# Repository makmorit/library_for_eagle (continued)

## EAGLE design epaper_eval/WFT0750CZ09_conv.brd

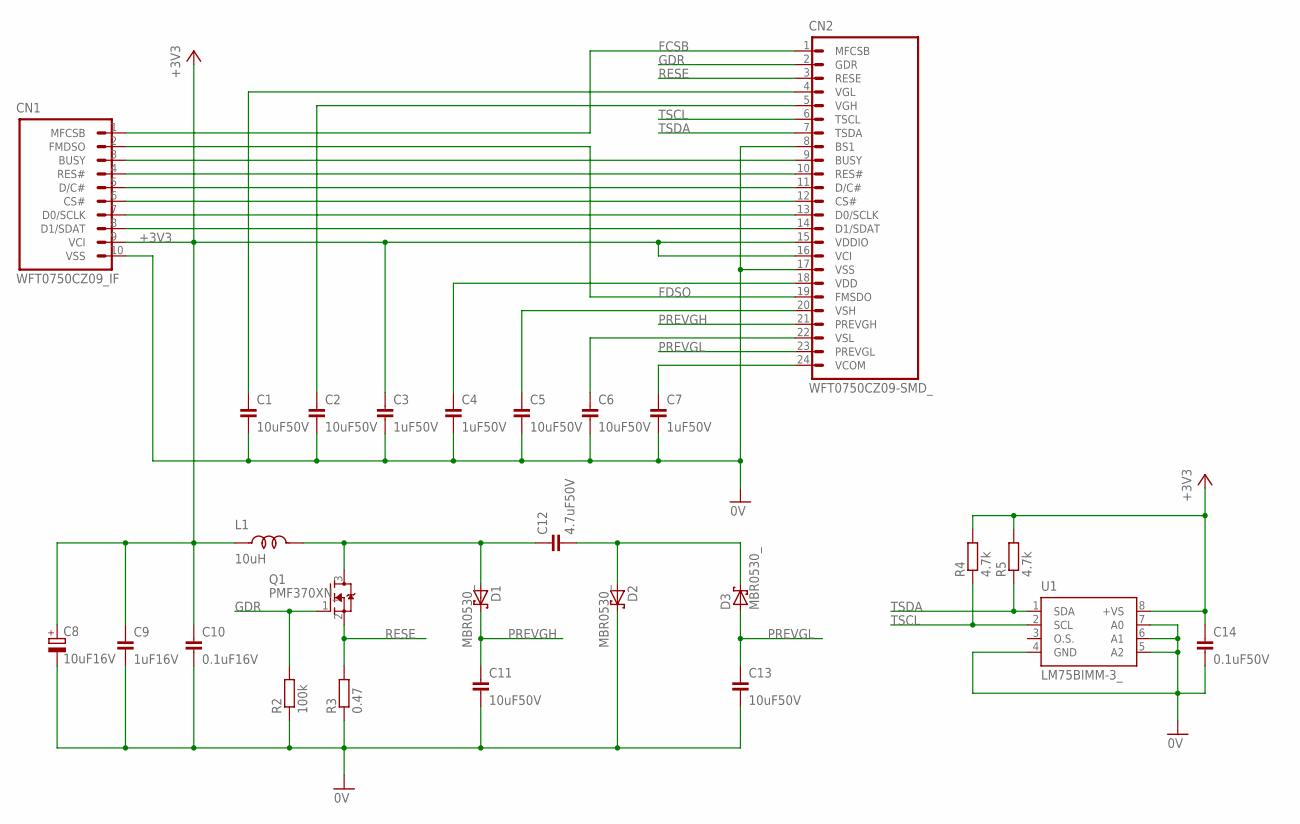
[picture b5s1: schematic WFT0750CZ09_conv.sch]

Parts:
C1, C2, C5, C6, C11, C13: 10uF50V; SMD_2012
C3, C4, C7: 1uF50V; SMD_2012
C8: 10uF16V; C1210_TPST_DEV
C9: 1uF16V; SMD_2012
C10: 0.1uF16V; SMD_2012
C12: 4.7uF50V; SMD_2012
C14: 0.1uF50V; SMD_2012
CN1: WFT0750CZ09_IF; WFT0750CZ09_IF_10PIN
CN2: WFT0750CZ09-SMD_; FH12A-24S-0.5SH_DEV
D1, D2, D3: MBR0530_; MBR0530_DEV
L1: 10uH; NLCV25T_DEV
Q1: PMF370XN_; SOT323_DEV
R2: 100k; SMD_2012
R3: 0.47; SMD_2012
R4, R5: 4.7k; SMD_2012
U1: LM75BIMM-3_; SSOP8-DGK_DEV

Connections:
0V: C1.2, C2.2, C3.2, C4.2, C5.2, C6.2, C7.2, C8.2 (-), C9.2, C10.2, C11.2, C13.2, C14.2, CN1.10 (VSS), CN2.8 (BS1), CN2.17 (VSS), D2.1 (C), R2.1, R3.1, U1.4 (GND), U1.5 (A2), U1.6 (A1), U1.7 (A0)
+3V3: C3.1, C8.1 (+), C9.1, C10.1, C14.1, CN1.9 (VCI), CN2.15 (VDDIO), CN2.16 (VCI), L1.1, R4.2, R5.2, U1.8 (+VS)
FCSB: CN1.1 (MFCSB), CN2.1 (MFCSB)
FDSO: CN1.2 (FMDSO), CN2.19 (FMSDO)
GDR: CN2.2 (GDR), Q1.1 (G), R2.2
unnamed: C7.1, CN2.24 (VCOM)
unnamed: C6.1, CN2.22 (VSL)
unnamed: C5.1, CN2.20 (VSH)
unnamed: C4.1, CN2.18 (VDD)
unnamed: C12.1, D1.2 (A), L1.2, Q1.3 (D)
unnamed: C2.1, CN2.5 (VGH)
unnamed: C1.1, CN2.4 (VGL)
unnamed: CN1.3 (BUSY), CN2.9 (BUSY)
unnamed: CN1.4 (RES#), CN2.10 (RES#)
unnamed: CN1.5 (D/C#), CN2.11 (D/C#)
unnamed: CN1.6 (CS#), CN2.12 (CS#)
unnamed: CN1.7 (D0/SCLK), CN2.13 (D0/SCLK)
unnamed: CN1.8 (D1/SDAT), CN2.14 (D1/SDAT)
unnamed: C12.2, D2.2 (A), D3.1 (C)
PREVGH: C11.1, CN2.21 (PREVGH), D1.1 (C)
PREVGL: C13.1, CN2.23 (PREVGL), D3.2 (A)
RESE: CN2.3 (RESE), Q1.2 (S), R3.2
TSCL: CN2.6 (TSCL), R4.1, U1.2 (SCL)
TSDA: CN2.7 (TSDA), R5.1, U1.1 (SDA)

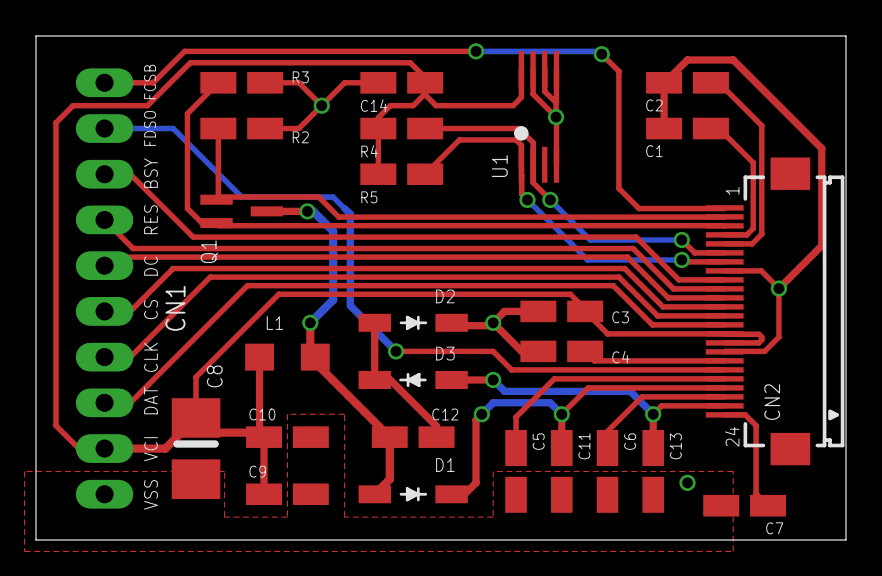
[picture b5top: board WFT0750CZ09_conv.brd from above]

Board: 2 copper layers, 45.0 x 28.0 mm, 26 parts (0 on the bottom side), 24 nets.

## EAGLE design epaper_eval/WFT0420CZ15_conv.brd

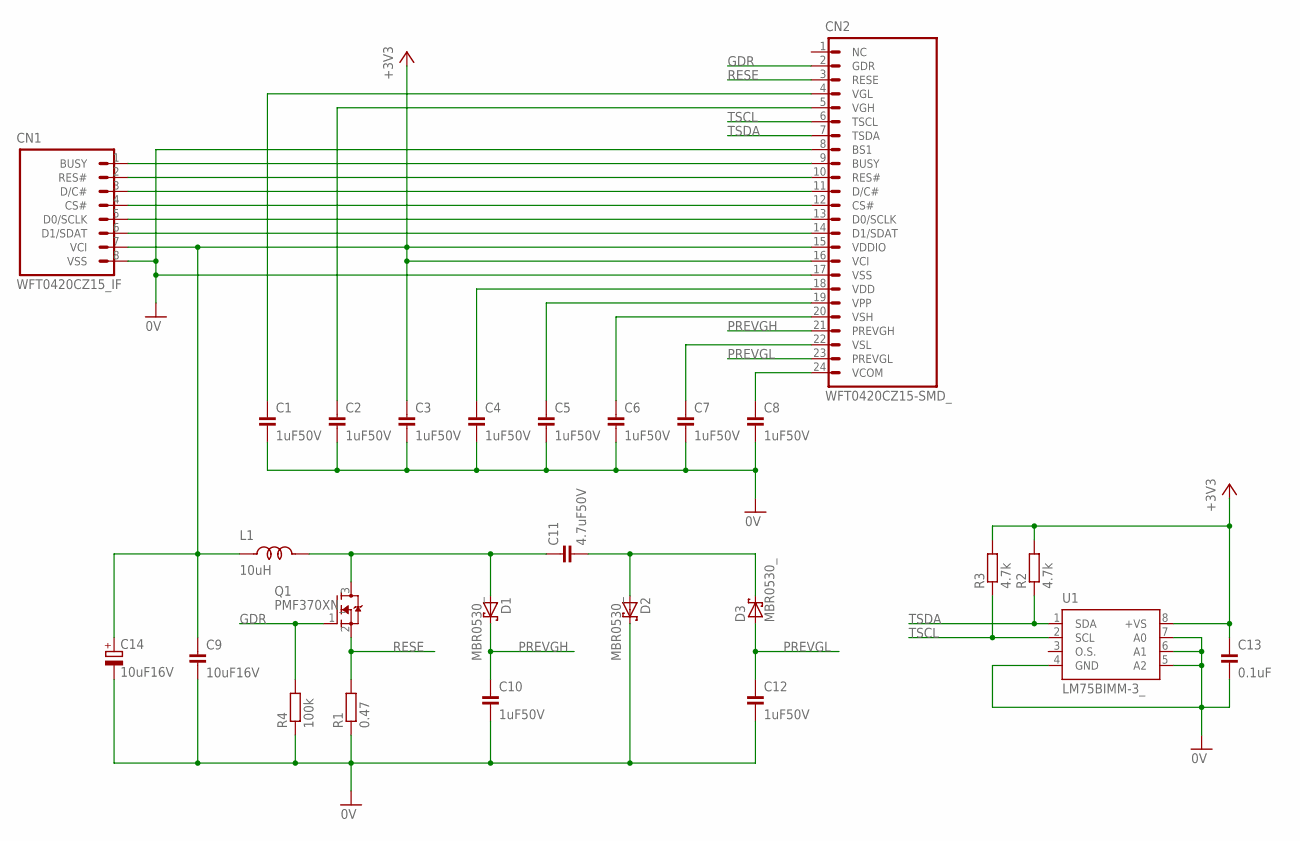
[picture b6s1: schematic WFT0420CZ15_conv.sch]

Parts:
C1, C2, C3, C4, C5, C6, C7, C8, C10, C12: 1uF50V; SMD_2012
C9: 10uF16V; SMD_2012
C11: 4.7uF50V; SMD_2012
C13: 0.1uF; SMD_2012
C14: 10uF16V; C1210_TPST
CN1: WFT0420CZ15_IF; WFT0420CZ15_IF_8PIN
CN2: WFT0420CZ15-SMD_; FH12A-24S-0.5SH_DEV
D1, D2, D3: MBR0530_; MBR0530_DEV
L1: 10uH; NLCV25T
Q1: PMF370XN_; SOT323_DEV
R1: 0.47; SMD_2012
R2, R3: 4.7k; SMD_2012
R4: 100k; SMD_2012
U1: LM75BIMM-3_; SSOP8-DGK_DEV

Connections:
0V: C1.2, C2.2, C3.2, C4.2, C5.2, C6.2, C7.2, C8.2, C9.2, C10.2, C12.2, C13.2, C14.2 (-), CN1.8 (VSS), CN2.8 (BS1), CN2.17 (VSS), D2.1 (C), R1.1, R4.1, U1.4 (GND), U1.5 (A2), U1.6 (A1), U1.7 (A0)
+3V3: C3.1, C9.1, C13.1, C14.1 (+), CN1.7 (VCI), CN2.15 (VDDIO), CN2.16 (VCI), L1.1, R2.2, R3.2, U1.8 (+VS)
GDR: CN2.2 (GDR), Q1.1 (G), R4.2
unnamed: C8.1, CN2.24 (VCOM)
unnamed: C7.1, CN2.22 (VSL)
unnamed: C6.1, CN2.20 (VSH)
unnamed: C5.1, CN2.19 (VPP)
unnamed: C4.1, CN2.18 (VDD)
unnamed: C11.1, D1.2 (A), L1.2, Q1.3 (D)
unnamed: C2.1, CN2.5 (VGH)
unnamed: C1.1, CN2.4 (VGL)
unnamed: CN1.1 (BUSY), CN2.9 (BUSY)
unnamed: CN1.2 (RES#), CN2.10 (RES#)
unnamed: CN1.3 (D/C#), CN2.11 (D/C#)
unnamed: CN1.4 (CS#), CN2.12 (CS#)
unnamed: CN1.5 (D0/SCLK), CN2.13 (D0/SCLK)
unnamed: CN1.6 (D1/SDAT), CN2.14 (D1/SDAT)
unnamed: C11.2, D2.2 (A), D3.1 (C)
PREVGH: C10.1, CN2.21 (PREVGH), D1.1 (C)
PREVGL: C12.1, CN2.23 (PREVGL), D3.2 (A)
RESE: CN2.3 (RESE), Q1.2 (S), R1.2
TSCL: CN2.6 (TSCL), R3.1, U1.2 (SCL)
TSDA: CN2.7 (TSDA), R2.1, U1.1 (SDA)

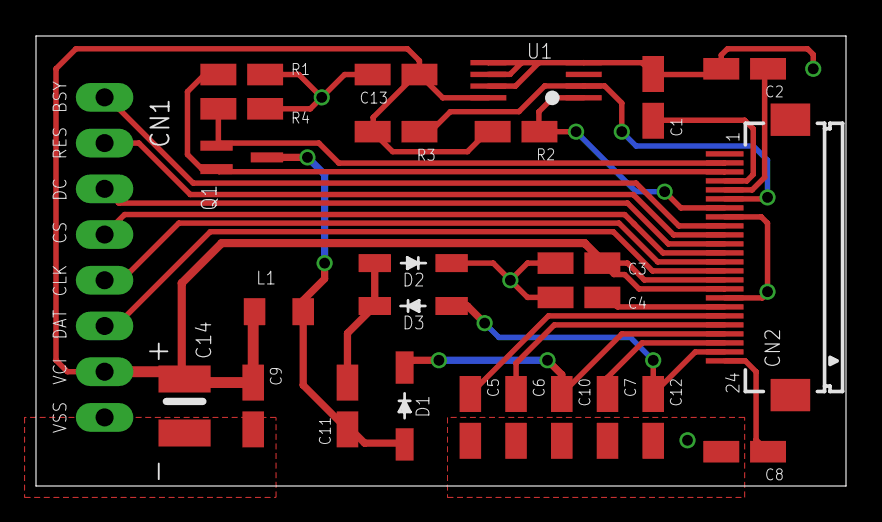
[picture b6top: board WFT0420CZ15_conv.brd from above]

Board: 2 copper layers, 45.0 x 25.0 mm, 26 parts (0 on the bottom side), 23 nets.

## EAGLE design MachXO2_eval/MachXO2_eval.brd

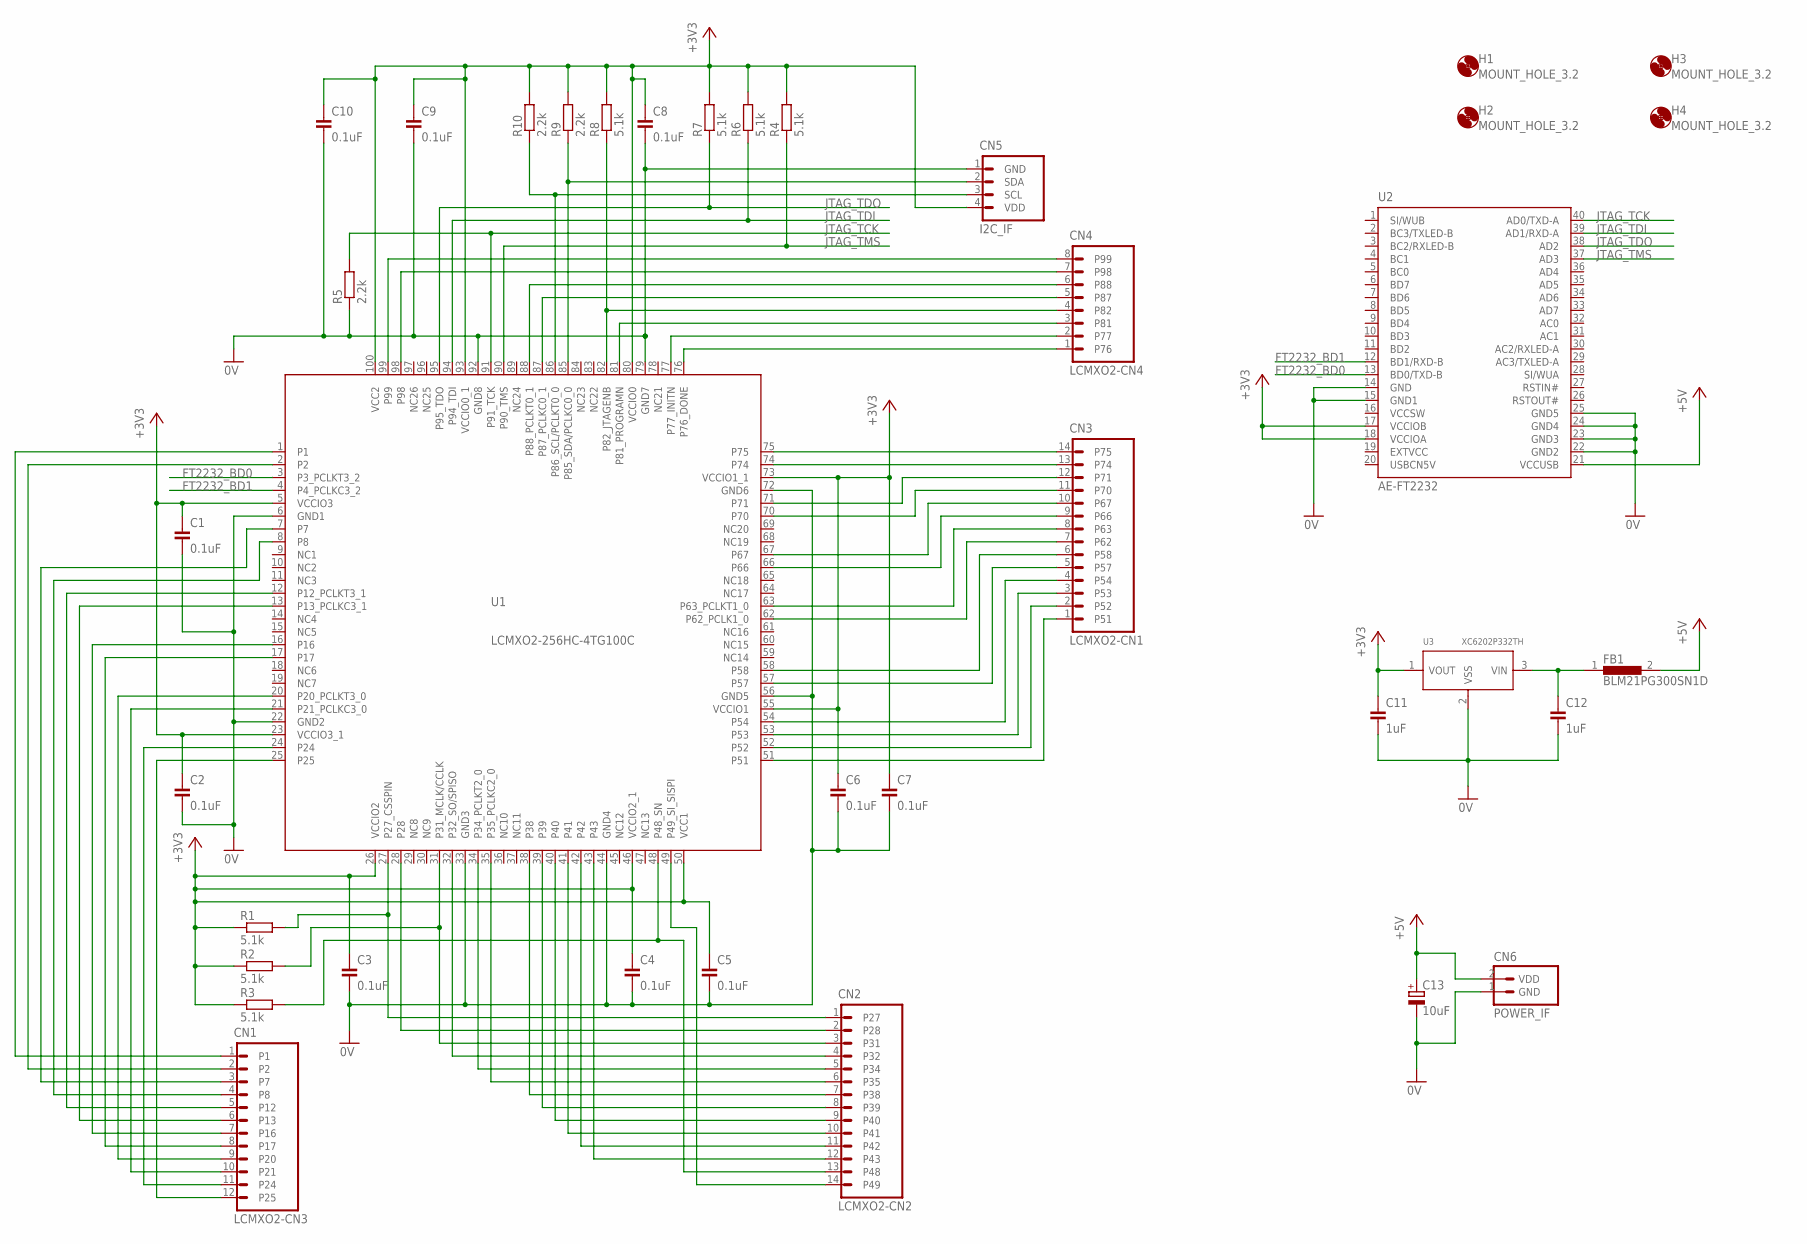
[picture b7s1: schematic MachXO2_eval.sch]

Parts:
C1, C2, C3, C4, C5, C6, C7, C8, C9, C10: 0.1uF; CAP_100MIL
C11, C12: 1uF; CAP_200MIL
C13: 10uF; ELECAP_200MIL
CN1: LCMXO2-CN3; LCMXO2-CN-3
CN2: LCMXO2-CN2; LCMXO2-CN-2
CN3: LCMXO2-CN1; LCMXO2-CN-1
CN4: LCMXO2-CN4; LCMXO2-CN-4
CN5: I2C_IF; I2C_IF_4PIN
CN6: POWER_IF; HEADER_2PIN_POWER_IF
FB1: BLM21PG300SN1D; SMD_2012
H1, H2, H3, H4: MOUNT_HOLE_3.2; 3,2
R1, R2, R3, R4, R6, R7, R8: 5.1k; RESISTOR_0204_200MIL
R5, R9, R10: 2.2k; RESISTOR_0204_200MIL
U1: LCMXO2-256HC-4TG100C; QFP100-0.5MMPITCH
U2: AE-FT2232; DIL40
U3: XC6202P332TH; TO92-LINE

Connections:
0V: C1.2, C2.2, C3.2, C4.2, C5.2, C6.2, C7.2, C8.2, C9.2, C10.2, C11.2, C12.2, C13.-, CN5.1 (GND), CN6.1 (GND), R5.1, U1.6 (GND1), U1.22 (GND2), U1.33 (GND3), U1.44 (GND4), U1.56 (GND5), U1.72 (GND6), U1.79 (GND7), U1.92 (GND8), U2.14 (GND), U2.15 (GND1), U2.22 (GND2), U2.23 (GND3), U2.24 (GND4), U2.25 (GND5), U3.2 (VSS)
+3V3: C1.1, C2.1, C3.1, C4.1, C5.1, C6.1, C7.1, C8.1, C9.1, C10.1, C11.1, CN5.4 (VDD), R1.1, R2.1, R3.1, R4.2, R6.2, R7.2, R8.2, R9.2, R10.2, U1.5 (VCCIO3), U1.23 (VCCIO3_1), U1.26 (VCCIO2), U1.46 (VCCIO2_1), U1.50 (VCC1), U1.55 (VCCIO1), U1.73 (VCCIO1_1), U1.80 (VCCIO0), U1.93 (VCCIO0_1), U1.100 (VCC2), U2.17 (VCCIOB), U2.18 (VCCIOA), U3.1 (VOUT)
+5V: C13.+, CN6.2 (VDD), FB1.2, U2.21 (VCCUSB)
FT2232_BD0: U1.3 (P3_PCLKT3_2), U2.13 (BD0/TXD-B)
FT2232_BD1: U1.4 (P4_PCLKC3_2), U2.12 (BD1/RXD-B)
I2C_SCL: CN5.3 (SCL), R10.1, U1.86 (P86_SCL/PCLKT0_0)
JTAG_TCK: R5.2, U1.91 (P91_TCK), U2.40 (AD0/TXD-A)
JTAG_TDI: R6.1, U1.94 (P94_TDI), U2.39 (AD1/RXD-A)
JTAG_TDO: R7.1, U1.95 (P95_TDO), U2.38 (AD2)
JTAG_TMS: R4.1, U1.90 (P90_TMS), U2.37 (AD3)
unnamed: CN4.4 (P82), R8.1, U1.82 (P82_JTAGENB)
unnamed: CN5.2 (SDA), R9.1, U1.85 (P85_SDA/PCLKC0_0)
unnamed: CN2.1 (P27), R1.2, U1.27 (P27_CSSPIN)
unnamed: CN3.4 (P54), U1.54
unnamed: CN3.3 (P53), U1.53
unnamed: CN3.10 (P67), U1.67
unnamed: CN3.9 (P66), U1.66
unnamed: CN2.3 (P31), R2.2, U1.31 (P31_MCLK/CCLK)
unnamed: CN3.8 (P63), U1.63 (P63_PCLKT1_0)
unnamed: CN2.13 (P48), R3.2, U1.48 (P48_SN)
unnamed: CN3.5 (P57), U1.57
unnamed: CN3.6 (P58), U1.58
unnamed: CN3.7 (P62), U1.62 (P62_PCLK1_0)
unnamed: CN2.14 (P49), U1.49 (P49_SI_SISPI)
unnamed: CN3.2 (P52), U1.52
unnamed: CN3.1 (P51), U1.51
unnamed: CN2.12 (P43), U1.43
unnamed: CN2.11 (P42), U1.42
unnamed: CN2.10 (P41), U1.41
unnamed: CN2.9 (P40), U1.40
unnamed: CN2.8 (P39), U1.39
unnamed: CN2.7 (P38), U1.38
unnamed: CN3.13 (P74), U1.74
unnamed: CN2.6 (P35), U1.35 (P35_PCLKC2_0)
unnamed: CN2.5 (P34), U1.34 (P34_PCLKT2_0)
unnamed: CN2.4 (P32), U1.32 (P32_SO/SPISO)
unnamed: CN2.2 (P28), U1.28
unnamed: CN3.11 (P70), U1.70
unnamed: CN3.12 (P71), U1.71
unnamed: CN3.14 (P75), U1.75
unnamed: CN4.1 (P76), U1.76 (P76_DONE)
unnamed: CN4.2 (P77), U1.77 (P77_INITN)
unnamed: C12.1, FB1.1, U3.3 (VIN)
unnamed: CN4.8 (P99), U1.99
unnamed: CN4.7 (P98), U1.98
unnamed: CN4.6 (P88), U1.88 (P88_PCLKT0_1)
unnamed: CN4.5 (P87), U1.87 (P87_PCLKC0_1)
unnamed: CN4.3 (P81), U1.81 (P81_PROGRAMN)
unnamed: CN1.12 (P25), U1.25
unnamed: CN1.11 (P24), U1.24
unnamed: CN1.10 (P21), U1.21 (P21_PCLKC3_0)
unnamed: CN1.9 (P20), U1.20 (P20_PCLKT3_0)
unnamed: CN1.8 (P17), U1.17
unnamed: CN1.7 (P16), U1.16
unnamed: CN1.6 (P13), U1.13 (P13_PCLKC3_1)
unnamed: CN1.5 (P12), U1.12 (P12_PCLKT3_1)
unnamed: CN1.4 (P8), U1.8
unnamed: CN1.3 (P7), U1.7
unnamed: CN1.2, U1.2
unnamed: CN1.1, U1.1

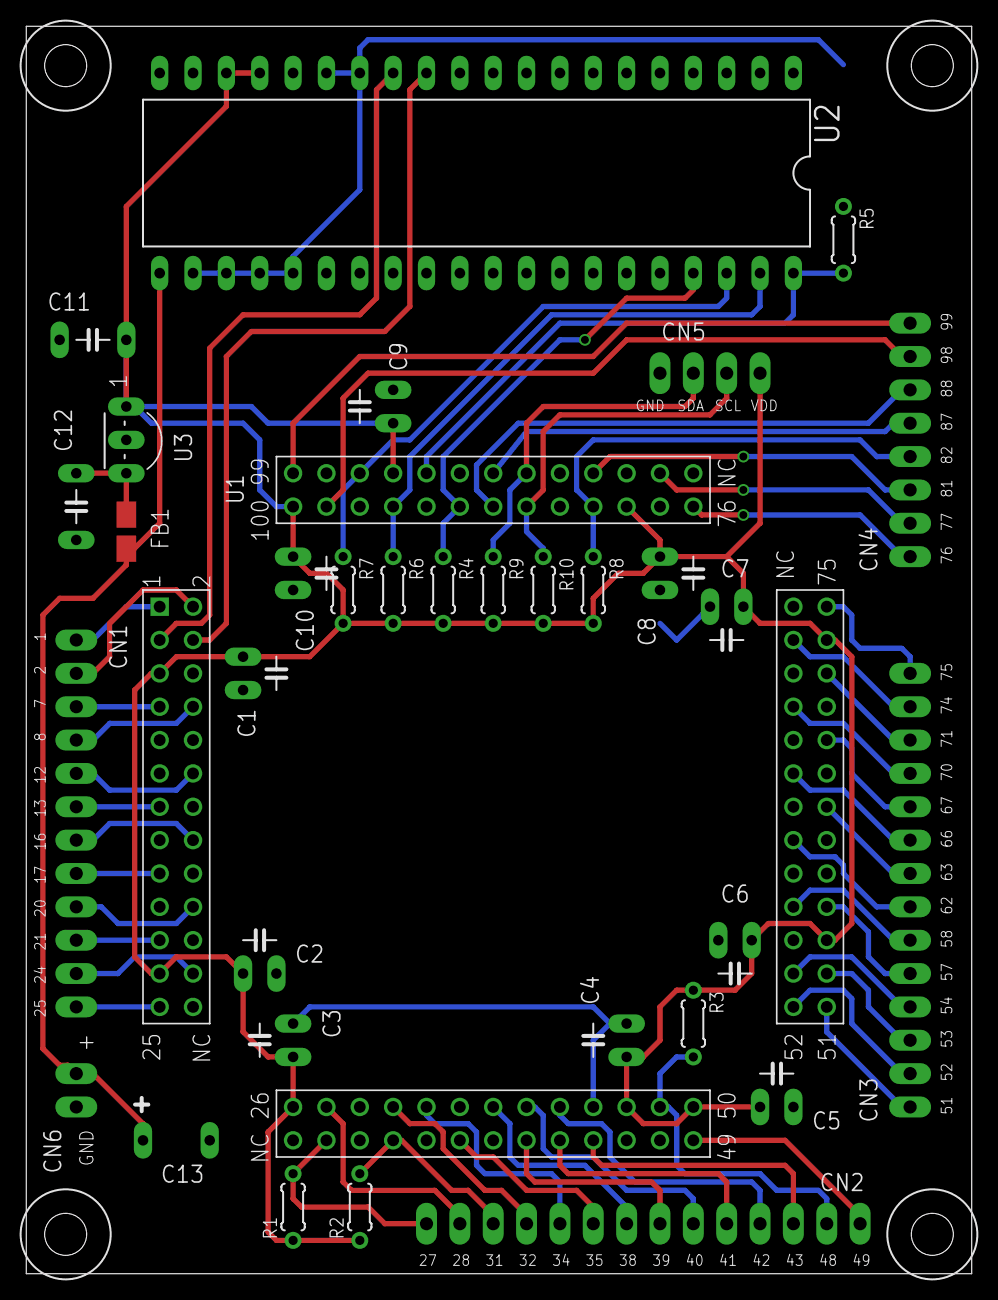
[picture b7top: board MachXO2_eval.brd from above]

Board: 2 copper layers, 72.0 x 95.0 mm, 37 parts (0 on the bottom side), 60 nets.

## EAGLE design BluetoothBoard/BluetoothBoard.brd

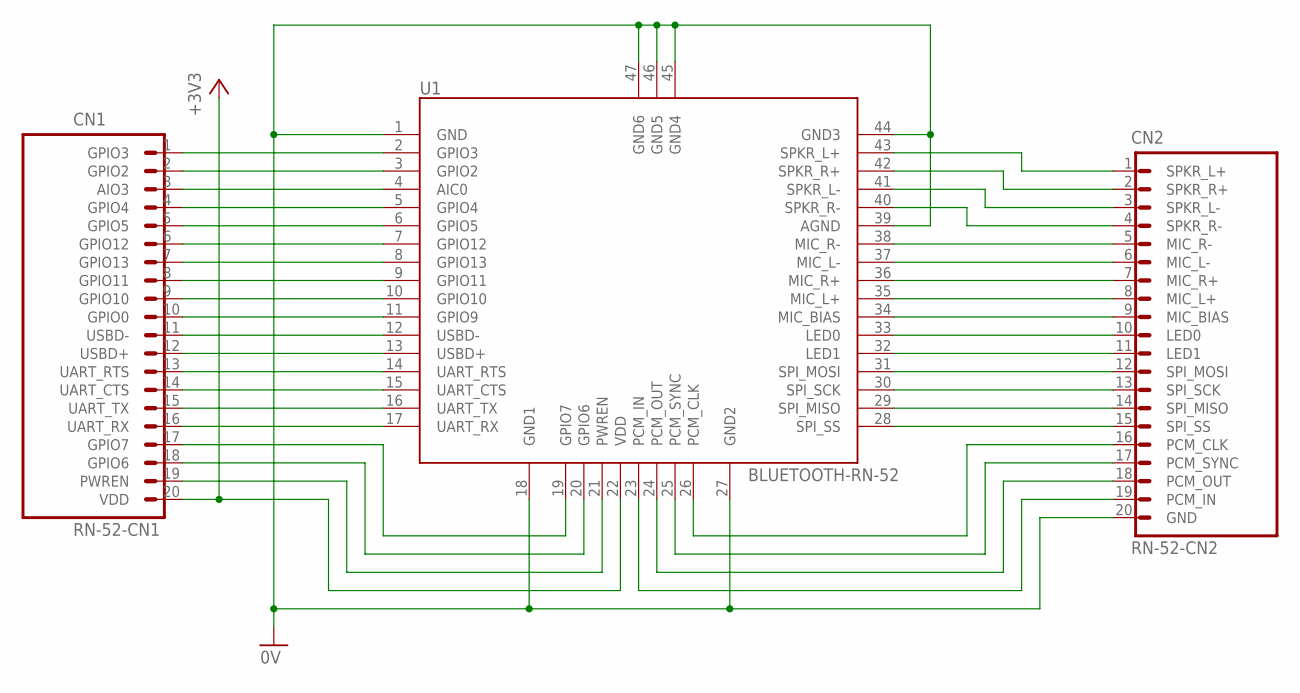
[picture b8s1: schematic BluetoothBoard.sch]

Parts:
CN1: RN-52-CN1
CN2: RN-52-CN2
U1: BLUETOOTH-RN-52; RN-52

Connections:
0V: CN2.20 (GND), U1.1 (GND), U1.18 (GND1), U1.27 (GND2), U1.39 (AGND), U1.44 (GND3), U1.45 (GND4), U1.46 (GND5), U1.47 (GND6)
+3V3: CN1.20 (VDD), U1.22 (VDD)
unnamed: CN1.1 (GPIO3), U1.2 (GPIO3)
unnamed: CN1.2 (GPIO2), U1.3 (GPIO2)
unnamed: CN1.3 (AIO3), U1.4 (AIC0)
unnamed: CN1.4 (GPIO4), U1.5 (GPIO4)
unnamed: CN1.5 (GPIO5), U1.6 (GPIO5)
unnamed: CN1.6 (GPIO12), U1.7 (GPIO12)
unnamed: CN1.7 (GPIO13), U1.8 (GPIO13)
unnamed: CN1.8 (GPIO11), U1.9 (GPIO11)
unnamed: CN1.9 (GPIO10), U1.10 (GPIO10)
unnamed: CN1.10 (GPIO0), U1.11 (GPIO9)
unnamed: CN1.11 (USBD-), U1.12 (USBD-)
unnamed: CN1.12 (USBD+), U1.13 (USBD+)
unnamed: CN1.13 (UART_RTS), U1.14 (UART_RTS)
unnamed: CN1.14 (UART_CTS), U1.15 (UART_CTS)
unnamed: CN1.15 (UART_TX), U1.16 (UART_TX)
unnamed: CN1.16 (UART_RX), U1.17 (UART_RX)
unnamed: CN1.17 (GPIO7), U1.19 (GPIO7)
unnamed: CN1.18 (GPIO6), U1.20 (GPIO6)
unnamed: CN1.19 (PWREN), U1.21 (PWREN)
unnamed: CN2.19 (PCM_IN), U1.23 (PCM_IN)
unnamed: CN2.18 (PCM_OUT), U1.24 (PCM_OUT)
unnamed: CN2.17 (PCM_SYNC), U1.25 (PCM_SYNC)
unnamed: CN2.15 (SPI_SS), U1.28 (SPI_SS)
unnamed: CN2.14 (SPI_MISO), U1.29 (SPI_MISO)
unnamed: CN2.13 (SPI_SCK), U1.30 (SPI_SCK)
unnamed: CN2.12 (SPI_MOSI), U1.31 (SPI_MOSI)
unnamed: CN2.11 (LED1), U1.32 (LED1)
unnamed: CN2.9 (MIC_BIAS), U1.34 (MIC_BIAS)
unnamed: CN2.4 (SPKR_R-), U1.40 (SPKR_R-)
unnamed: CN2.3 (SPKR_L-), U1.41 (SPKR_L-)
unnamed: CN2.2 (SPKR_R+), U1.42 (SPKR_R+)
unnamed: CN2.5 (MIC_R-), U1.38 (MIC_R-)
unnamed: CN2.6 (MIC_L-), U1.37 (MIC_L-)
unnamed: CN2.7 (MIC_R+), U1.36 (MIC_R+)
unnamed: CN2.8 (MIC_L+), U1.35 (MIC_L+)
unnamed: CN2.16 (PCM_CLK), U1.26 (PCM_CLK)
unnamed: CN2.10 (LED0), U1.33 (LED0)
unnamed: CN2.1 (SPKR_L+), U1.43 (SPKR_L+)

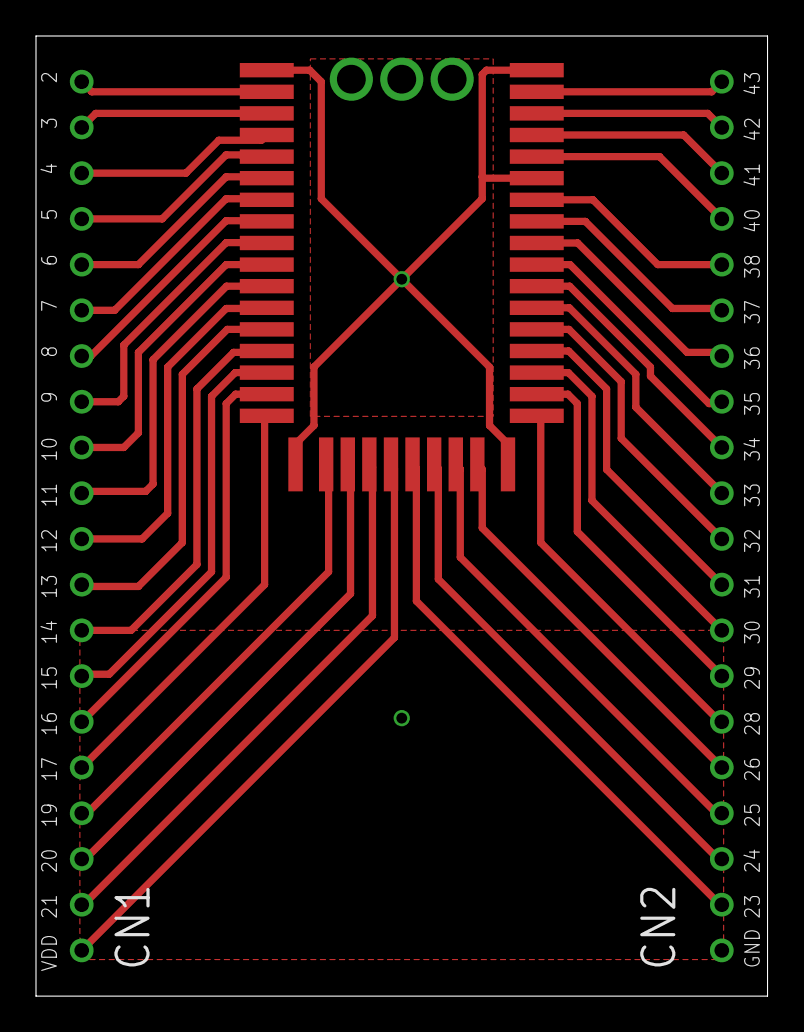
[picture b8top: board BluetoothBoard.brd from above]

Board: 2 copper layers, 40.6 x 53.3 mm, 3 parts (0 on the bottom side), 40 nets.

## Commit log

2017-04-06 ツールファイルの初版
    ・ガーバー出力ツール
    ・デザインチェック用ツール
2017-04-08 デバイス追加
    PIC16F18877
2017-04-08 デバイス追加
    ２ピンコネクター
2017-04-08 デバイス修正
    PIC16F18877 の I2C ピン記述を修正
2017-04-09 デバイス追加
2017-04-12 プロトタイプ用の部品初版
2017-04-12 デバイス追加
    ジャンパーピン
2017-04-12 プロト用部品修正
    AE-FT2232
    AE_ESP-WROOM-02
2017-04-12 サンプルを追加
    ２セットの AE-ESP-WROOM-02 をメンテナンスするための基板
2017-04-19 パッケージを追加
    ・5mm幅の小型抵抗器
2017-04-24 デバイス追加
    I2C温度センサー
2017-04-29 サンプルを追加
    MachXO2をメンテナンスするための基板
2017-04-30 デバイス追加
    PIC16F18857
2017-05-09 デバイス追加
    LPC810、M25PX16
2017-05-21 PartsForProto.lbrを集約
2017-05-21 ピンを増設
    ・動作確認用のピンを基板外に出すための配線を追加
    ・外部電源コネクターとケミコンを追加
2017-05-22 MachXO2評価基板修正
    外出しピンを追加
2017-05-23 RN-52変換基板デザインの初版
2017-05-24 MachXO2評価基板修正
    外出し用のピンを追加
2017-05-25 MachXO2評価基板修正
    外出し用のピンをさらに追加
2017-05-26 PartsForProtoをマージ
    プロジェクトごとに分散しているデータを集約
    （まだ他にも存在する可能性があります）
2017-05-28 デバイス追加
    RTC-8564NBモジュール(秋月)
2017-05-29 デバイス追加
    CR2032（3Vボタン乾電池）
2017-06-05 デバイス追加
    マイクロＳＤカードスロットＤＩＰ化キット
2017-06-15 デバイス追加
    MINMAXのレギュレーター
2017-06-16 デバイス修正
    AE-ESP-WROOM-02の外形データを追加
2017-06-17 デバイス修正
2017-06-18 デバイス修正
    ジャンパーのtPlaceがかぶっていたので修正
2017-06-24 デバイス追加
    リードインダクター
2017-06-26 デバイス追加
    電池ホルダー（CR2032）
2017-06-27 デバイス修正
    microSD変換基板用コネクターの番号
2017-06-29 デバイス追加
    PIC GPIOインターフェース
2017-07-04 デバイス修正
    シルクが間違っていたので修正
2017-07-07 デバイス修正
    microSDカードスロット変換基板の外形データを追加
2017-07-07 デバイス修正
    セラミックコンデンサーのパターンを見直し
2017-07-08 デバイス修正
    AE-AQM1602Aの外形データを追加
2017-07-09 デバイス修正
    シルク位置・大きさ
2017-07-15 デバイス修正
    外形データを追加、コメントが間違っているので修正
2017-07-16 パッケージ追加
    10pinSMDヘッダー
2017-07-17 シンボル追加
    10Pin インターフェース
    （鉄道模型コントローラー基板用）
2017-07-18 デバイス追加
    10Pin インターフェース
    （鉄道模型コントローラー基板用）
2017-07-19 パッケージ追加
    20pinSMDヘッダー
2017-07-21 シンボル追加
    20Pin インターフェース
    （鉄道模型コントローラー基板用）
2017-07-22 デバイス追加
    20Pin インターフェース
    （鉄道模型コントローラー基板用）
2017-07-25 パッケージ修正
    シルクのサイズを小さく変更
2017-07-27 デバイス修正
    3mm砲弾型LED追加
2017-07-29 デバイス追加
    SI1308EDL
    LM75BIMM-3
2017-07-30 デバイス追加
    MBR0530
    NLCV25T
2017-07-30 デバイス追加
    WF0420CZ15
2017-07-31 デバイス追加
    WF0420CZ15変換基板用I/F
2017-08-01 パッケージ修正
    シルクのサイズを縮小
2017-08-01 e-paper I/F基板の初版
2017-08-02 部品を追加
2017-08-03 レイアウト変更
    概ね確定です
2017-08-11 パッケージ修正
    ニキシー管のシルクを調整
2017-08-13 パッケージ追加
    ニキシー管I/F
2017-08-15 パッケージ追加
    電解コンデンサー（足の狭いやつ）
2017-09-04 デバイス追加
    ・FH12A-24S-0.5SHの手はんだ用パターン追加
    ・PMF370XN（品番違いの同パッケージ）追加
    ・LM75の手はんだ用パターンでないパッケージを追加
2017-09-04 パッケージ変更
    開発用パッケージ（手はんだ用パターン）のパッケージ名称を _DEV に変更
    一部デバイスについて、本番用パッケージを追加
2017-09-13 新バージョンの初版
2017-09-15 部品配置を修正
2017-09-15 部品配置の小修正
2017-10-22 パッケージ変更
    0805パターンの正式版（手はんだ用バージョンでないもの）を追加
2017-10-26 パッケージ変更
    シルクのサイズと位置
2018-01-12 基板デザイン
2018-01-20 基板デザイン修正
2018-02-02 部品変更
2018-02-02 評価基板を追加
2018-02-04 パッケージ追加
2018-02-07 デバイス追加
    STM32F767ZI
2018-03-09 デバイス追加
    ・STM32F767ZIおよび評価用部品を追加登録
    ・eagleのバージョンを7.5.0--->7.7.0へ変更
2018-03-09 不要リソースを削除
2018-03-10 評価基板を追加
    ・オプションデバイスを追加搭載
2018-03-11 パッケージ修正
    ・手はんだ用パターンを追加
2018-03-11 評価基板を修正
    ・手はんだ用パターンに修正
2018-03-11 評価基板を修正
    ・シルクの位置などを調整
2018-03-11 評価基板を修正
    ・バイパスコンデンサー修正
    ・配線欠落箇所を修正
2018-03-12 評価基板を修正
    ・電源回路の出力側にバイパスコンデンサーを追加
2018-03-14 評価基板を修正
    ・定数記述を修正
2018-03-16 評価回路を追加
    ・基板デザインはありません
2018-03-16 評価回路を修正
2018-03-24 シンボル追加
2018-03-26 パッケージ修正
    ・中央点を移動
2018-03-26 モジュール追加
2018-03-27 評価回路を修正
    ・オプションデバイス追加
2018-03-29 パッケージ修正
    ・シルクをずらす
2018-03-29 評価回路を修正
    ・デバイス追加に伴い、配線パターンを大幅に変更
2018-03-30 評価回路を修正
    ・VCAP_1、VCAP_2の配線が間違っていたので修正
2018-03-30 評価回路を修正
    ・手はんだパターンに修正
2018-03-31 評価回路を修正
    ・オプションデバイス電圧とメイン電圧間にジャンパーを挿入
2018-04-01 評価回路を修正
    ・コメント修正
2018-04-01 評価回路を修正
    ・回り込んだ配線を見直して修正
2018-04-01 評価回路を修正
    ・手はんだパターンに置換え
2018-04-01 評価回路を修正
    ・配線を修正
    ・+1V8のNAMEが不正だったので修正
2018-04-03 回路図初版
2018-04-05 回路図修正
    ・SIMスロット、アンテナコネクターを追加、配線
2018-04-06 デバイス追加
    ・評価回路用のコネクター
2018-04-08 回路図修正
    ・動作確認用LED、スイッチ類を追加
2018-04-08 回路図修正
2018-04-08 回路図修正
    ・UART用のレベル変換回路を追加
2018-04-09 回路図修正
    ・UARTインターフェースコネクターと、その配線を追加
2018-04-09 回路図修正
    ・Arduino互換インターフェース追加
    ・不要な配線を削除
    ・VRTCにパスコンを為念接続
2018-04-12 パッケージを追加
    ・ブレークアウト用半穴
2018-04-13 ブレークアウト基板初版
    ・外形データを入れてDRC実行すると、エラーになるため、外形データは省略しています。ガーバー出力時に外形データを入れるようにしてください。
2018-04-13 デバイス修正
    ・ブレークアウトのピン数を32--->36に拡張
2018-04-14 デザイン修正
    ・ブレークアウト基板のピンレイアウトを修正
2018-04-19 デザイン修正
    ・ピンレイアウト修正
2018-04-22 モジュール修正
    ・ブレークアウト基板使用前提のパッケージを追加
2018-04-24 評価回路を修正
    ・PCBデザインはWIP
2018-04-24 [WIP] デザイン修正
2018-04-25 デザイン修正
    ・配線パターンを見直し
2018-04-25 配線を全面的に修正
2018-04-26 評価回路を修正
    ・配線を小修正
2018-04-26 デザイン修正
    ・パターンを小修正
2018-04-30 デバイス追加
    ・MCP1501
    ・MCP3221
2018-05-04 デバイス修正
    ・パッケージデータが全く違っていたので修正
2018-05-08 評価用デバイスの登録
2018-05-08 回路図を修正
    ・部品のパッケージを入れ替え
    ・セキュリティーチップ回路図のシートを移動
2018-05-09 回路図を修正
    ・構成部品を入替え
2018-05-09 回路図を修正
    ・回路図のレイアウトを修正
    ・定数変更
2018-05-09 回路図を修正
    ・回路図のレイアウトを修正
    ・ダンピング抵抗追加
2018-05-09 デバイス追加
    ・MICS-5524
    ・DMG3415U
2018-05-12 デバイス追加
    ・MIC5205
2018-05-13 回路図を修正
    ・ST-LINK V2-1インターフェースを他部品に変更
    ・外部フラッシュの電源をSTMの電源と切り離す
    ・Groveコネクターを基板の隅に移動
2018-05-14 パッケージ修正
    ・１番ピンマークの位置を変更
2018-05-14 回路図を修正
    ・配線変更
2018-05-15 レイアウトを修正
    ・デザインルールチェック済み第１版
2018-05-15 レイアウトを修正
    ・通信モジュール用のUARTピンの位置を変更
2018-05-16 レイアウトを修正
    ・外部RX、TXはArduinoアナログピンを流用させるよう実装変更
2018-05-16 レイアウトを修正
    ・近接していた部品を移動
2018-05-22 ライブラリー整理
    ・不要な回路図・デバイスを削除
2018-05-22 デバイス修正
    ・専用インターフェースピンを廃止して汎用インターフェースと置換え
2018-06-04 ライブラリーを更新
    ・不要なデバイス、ライブラリーファイルを削除
2018-06-05 パッケージ修正
2018-06-10 デバイス修正
    ・LDL112--->LDL212に変更
2018-06-13 デバイス修正
    ・手はんだパターン用パッケージを追加
2018-06-19 デバイス修正
    ・不要な部品は削除しました
2018-07-22 パッケージ修正
    ・互換ピンのシルクサイズ／向きを修正
2018-07-31 パッケージを差替え
2018-08-13 デバイスを追加／修正
2018-08-15 ドキュメントテンプレート修正
2018-08-15 デバイス追加／修正
2018-08-26 パッケージ修正
    ・外形ラインをシルクに追加
2018-09-23 デバイス修正
    ・外形シルクを追加
    ・手はんだ用パターンを修正
2019-02-10 モジュール追加
    ・ESP-WROOM-02
2019-05-16 デバイス修正
    ・USBプラグ
2019-05-30 デバイスを追加
    ・SKTADAE010
2019-05-30 デバイス追加
    ・APHF1608LSEEQBDZGKC
    ・NSR0620P2T5G
    ・XC6206
2019-06-13 デバイス追加
    ・PMEG2005
2019-06-20 デバイス追加
    ・BAT-HLD-012-SMT
2019-06-20 デバイス追加
    ・AS3956
2020-02-04 パッケージを修正
    ・シルクデータを修正
    ・一部表面実装部品のパッド幅を変更（狭くしました）
    ・一部部品のコメントに間違いがあったので修正
2020-04-30 パッケージを修正
    ・バイパスコンデンサーについて、パッドのはんだパターンが離れているものを追加
2020-04-30 デバイスを修正
    ・３ピンインターフェース用のパッドを追加
    ・フェライトビーズについて、パッドのはんだパターンが離れているものを追加
2020-07-08 デバイス追加
    ・LED部品を追加
    ・LED用パッケージを追加
    ・SMDジャンパーパターンを追加
2020-07-16 デバイス修正
    ・1608用パッドパターンを追加
2021-01-16 デバイス追加
    ・87520-0010BLF
    ・CX60-24S-UNIT
2021-01-22 デバイスを修正
    ・CX60-24S-UNIT：配線が間違っていたので修正
    ・87520-0010BLF：外形データを追加
2021-01-22 評価用基板を作成
2021-01-23 評価用基板を修正
    ・CCの配線（プルダウン抵抗）が抜けていたので追加
    ・テスト用ホールの位置を修正
    ・プラグB面のD+、D-は不要なので削除
2021-01-24 評価用基板を修正
    ・配線パターンを修正
2021-02-27 デバイス追加
    ・USBULC6
    ・MIC5323
    ・LDK120
    ・NSR0520V2
2021-02-28 デバイス修正
    ・品番を追加
2021-02-28 評価用基板の回路図
2021-05-08 デバイス追加
    ・Keystone Electronics 1072TR
2022-03-08 デバイス追加
    ・BT40
2022-03-09 デバイス追加
    ・Molex 2137160001
2022-03-10 デバイス追加
    ・ADP122
2022-03-14 パッケージを修正
    ・はんだパッド（４点）を追加
2022-04-14 デバイス追加
    ・USB4105-GF-A
2022-05-11 パッケージを修正
    ・抵抗器のkeepoutを外す（不要な為）
    ・USBコネクターの取り付け穴を拡張
2022-05-11 デバイスを追加
    ・RV-3028-C7
2022-05-30 デバイスを修正
    ・6-pinインターフェースを差替
2022-06-10 パッケージを修正
    ・パッド間の幅 > 0.2mm となるよう修正
2022-07-04 パッケージを修正
    ・取り付け穴部を両面パッドに修正
2022-09-29 デバイスを追加
    ・MDBT53
    （Raytac社のデータから転載＆一部修正）
2022-09-29 デバイスを修正
    ・BAT-HLD-012-SMT
    ・USB4105-GF-A
2022-10-08 デバイスを追加
    ・BAT-HLD-003-SMT
2022-10-08 パッケージを追加
    ・DFN1006D-2
    ・R0402N
2022-10-08 デバイスを追加
    ・RESISTOR_0402N
    ・XC6206P302MR-G
    ・PMEG2005BELD,315
2022-10-09 パッケージを修正
    ・チップ部品のランドパターンを追加
2022-10-11 デバイスを追加
    ・認識マーク
2023-02-09 デバイスを追加
    ・USB4155-03-C
2023-02-24 デバイスを追加
    ・51296-0894（Molex）
2023-02-27 [WIP] パッケージを追加
    ・BSS84AKQB
2023-02-27 デバイスを追加
    ・BSS84AKQB
2023-03-25 デバイスを修正
    ・APHF1608LSEEQBDZGKC
2023-03-27 パッケージを修正
    ・BSS84AKQB
2023-04-28 デバイスを追加
    ・FC-135
2024-07-22 デバイスを修正
    ・HEADER_2PIN
2024-08-12 デバイスを追加
    ・REF33
    ・MCP6232
2024-08-15 ライブラリーを追加
    ・チップ部品に特化したライブラリーを新設
2024-08-15 デバイスを追加
    ・チップコンデンサー（３点）
2024-08-15 デバイスを追加
    ・チップ抵抗器（２点）
2024-08-15 デバイスを追加
    ・FCC16
2024-08-15 デバイスを追加
    ・PMEG4010
2024-08-15 デバイスを追加
    ・BC817
2024-08-15 デバイスを追加
    ・DMP2035
2024-08-15 デバイスを追加
    ・SN74AHC1G00
2024-08-15 デバイスを修正
2024-08-15 シンボルを修正
